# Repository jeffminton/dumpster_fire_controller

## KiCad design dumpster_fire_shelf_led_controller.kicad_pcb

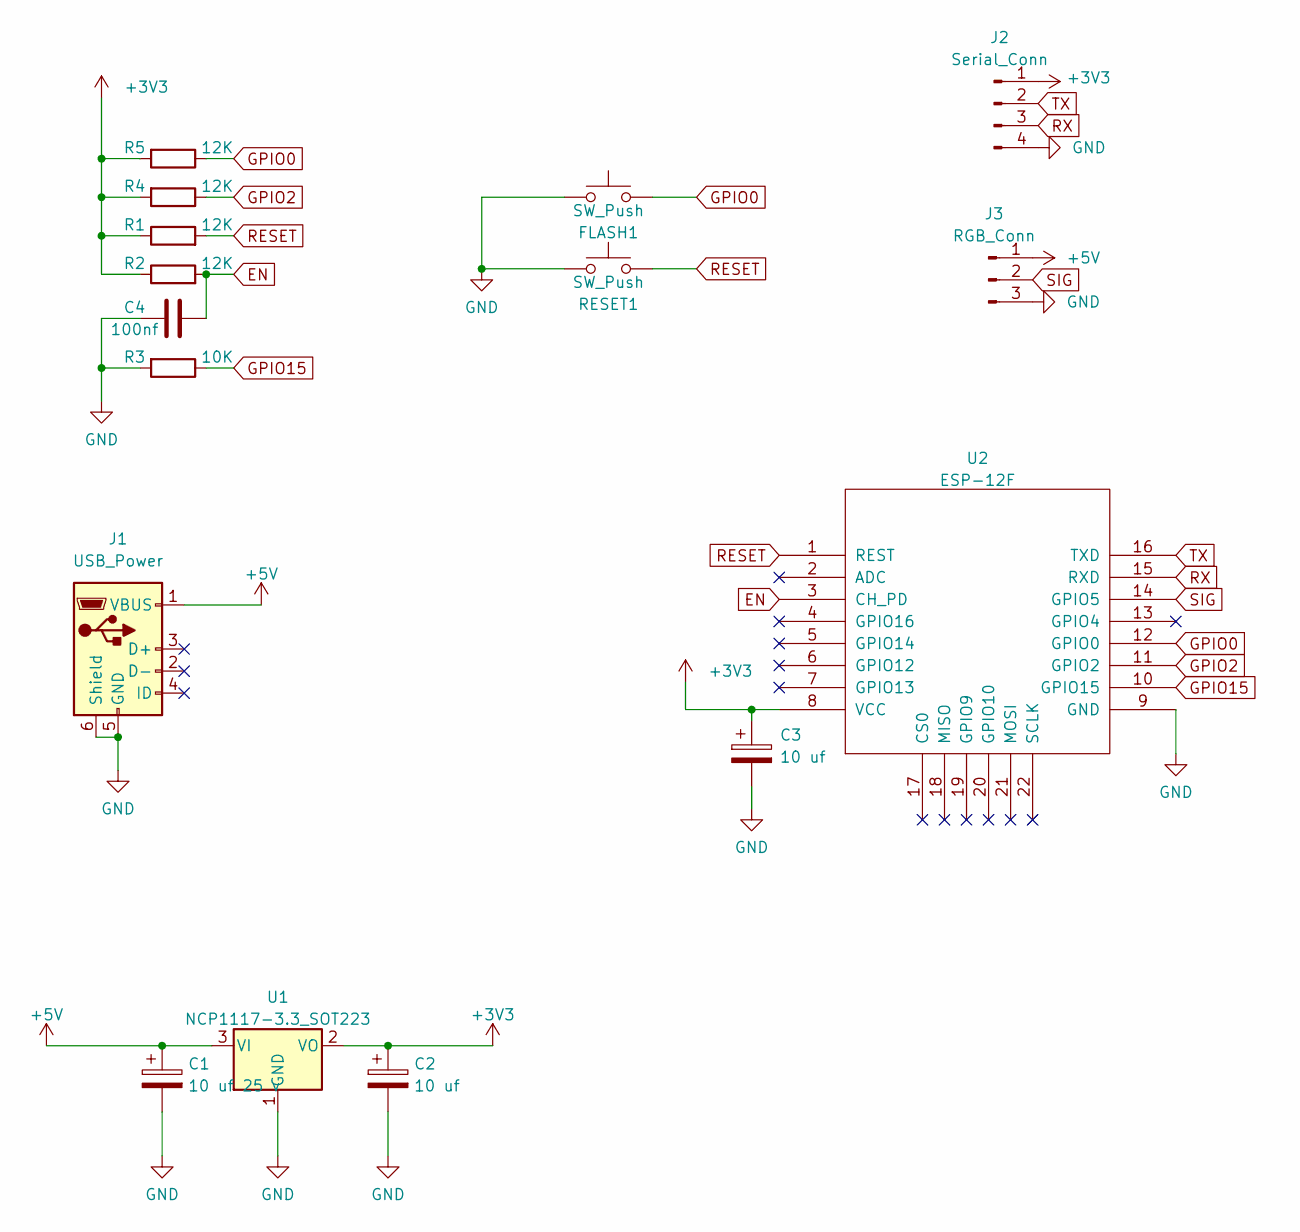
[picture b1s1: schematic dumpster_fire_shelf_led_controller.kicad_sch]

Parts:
C1: 10 uf 25 v; CP_EIA-3216-18_Kemet-A_Pad1.58x1.35mm_HandSolder
C2, C3: 10 uf; CP_EIA-3216-18_Kemet-A_Pad1.58x1.35mm_HandSolder
C4: 100nf; C_1206_3216Metric_Pad1.33x1.80mm_HandSolder
FLASH1: SW_Push; SW_SPST_TL3305A
J1: USB_Power; USB_Micro-B_GCT_USB3076-30-A
J2: Serial_Conn; Harwin_M20-89004xx_1x04_P2.54mm_Horizontal
J3: RGB_Conn; 2060-453_998-404 3 POS
R1, R2, R4, R5: 12K; R_0805_2012Metric_Pad1.20x1.40mm_HandSolder
R3: 10K; R_0805_2012Metric_Pad1.20x1.40mm_HandSolder
RESET1: SW_Push; SW_SPST_TL3305A
U1: NCP1117-3.3_SOT223; SOT-223-3_TabPin2
U2: ESP-12F; ESP-12E_SMD

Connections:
+3V3: C2.1, C3.1, J2.1, R1.1, R2.1, R4.2, R5.2, U1.2 (VO), U2.8 (VCC)
+5V: C1.1, J1.1 (VBUS), J3.1, U1.3 (VI)
EN: C4.2, R2.2, U2.3 (CH_PD)
GND: C1.2, C2.2, C3.2, C4.1, FLASH1.1, J1.5 (GND), J1.6 (Shield), J2.4, J3.3, R3.2, RESET1.1, U1.1 (GND), U2.9 (GND)
GPIO0: FLASH1.2, R5.1, U2.12 (GPIO0)
GPIO2: R4.1, U2.11 (GPIO2)
GPIO15: R3.1, U2.10 (GPIO15)
RESET: R1.2, RESET1.2, U2.1 (REST)
RX: J2.3, U2.15 (RXD)
SIG: J3.2, U2.14 (GPIO5)
TX: J2.2, U2.16 (TXD)

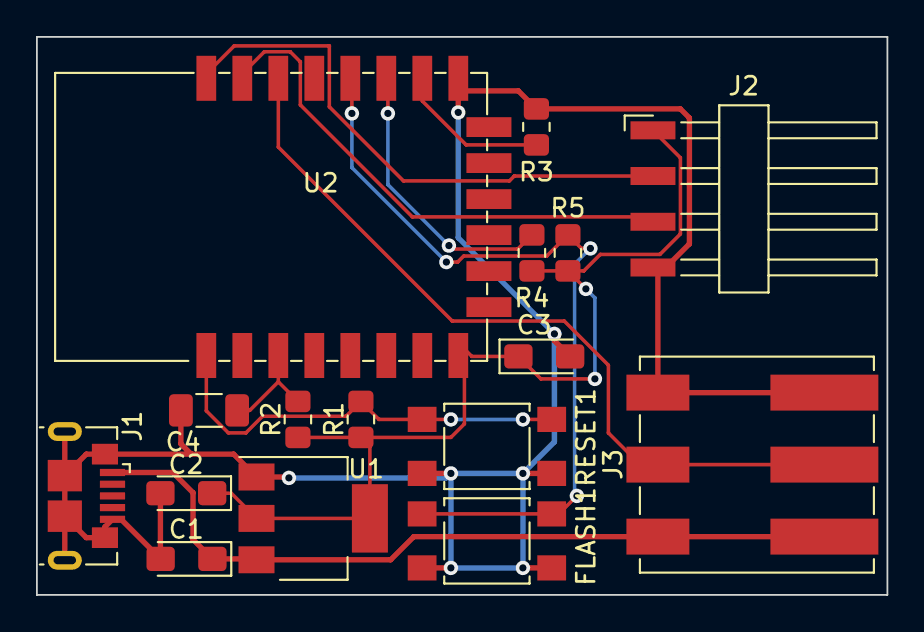
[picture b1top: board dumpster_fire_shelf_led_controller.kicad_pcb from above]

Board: 2 copper layers, 47.2 x 31.0 mm, 16 parts (0 on the bottom side), 11 nets.

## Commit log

2023-10-13 init commit
2023-10-13 init commit 2
